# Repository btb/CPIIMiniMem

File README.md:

# Compaq Portable II Mini Memory Expansion

## TODO

More investigation of the possibility of using higher-density SIMMs.

SIMM socket just a smidge too close to the ICs. They'll hit if the ICs use sockets.

Placement of Bank3-4 expanson connector probably renders the nearby mounting hole useless.

Overlap of Bank3-4 expansion connector with SIMM socket not ideal.

SIMM could be turned around and hang over battery.

Can probably make a few mm bigger.

Would be nice if main connector was easier to align.

Find correct size standoffs.

## About

This is a 512K expansion board which connects directly to the motherboard of the Compaq Portable II.

Based on the reverse-engineered [System Memory Board](https://github.com/btb/PortableIIMemBoard).

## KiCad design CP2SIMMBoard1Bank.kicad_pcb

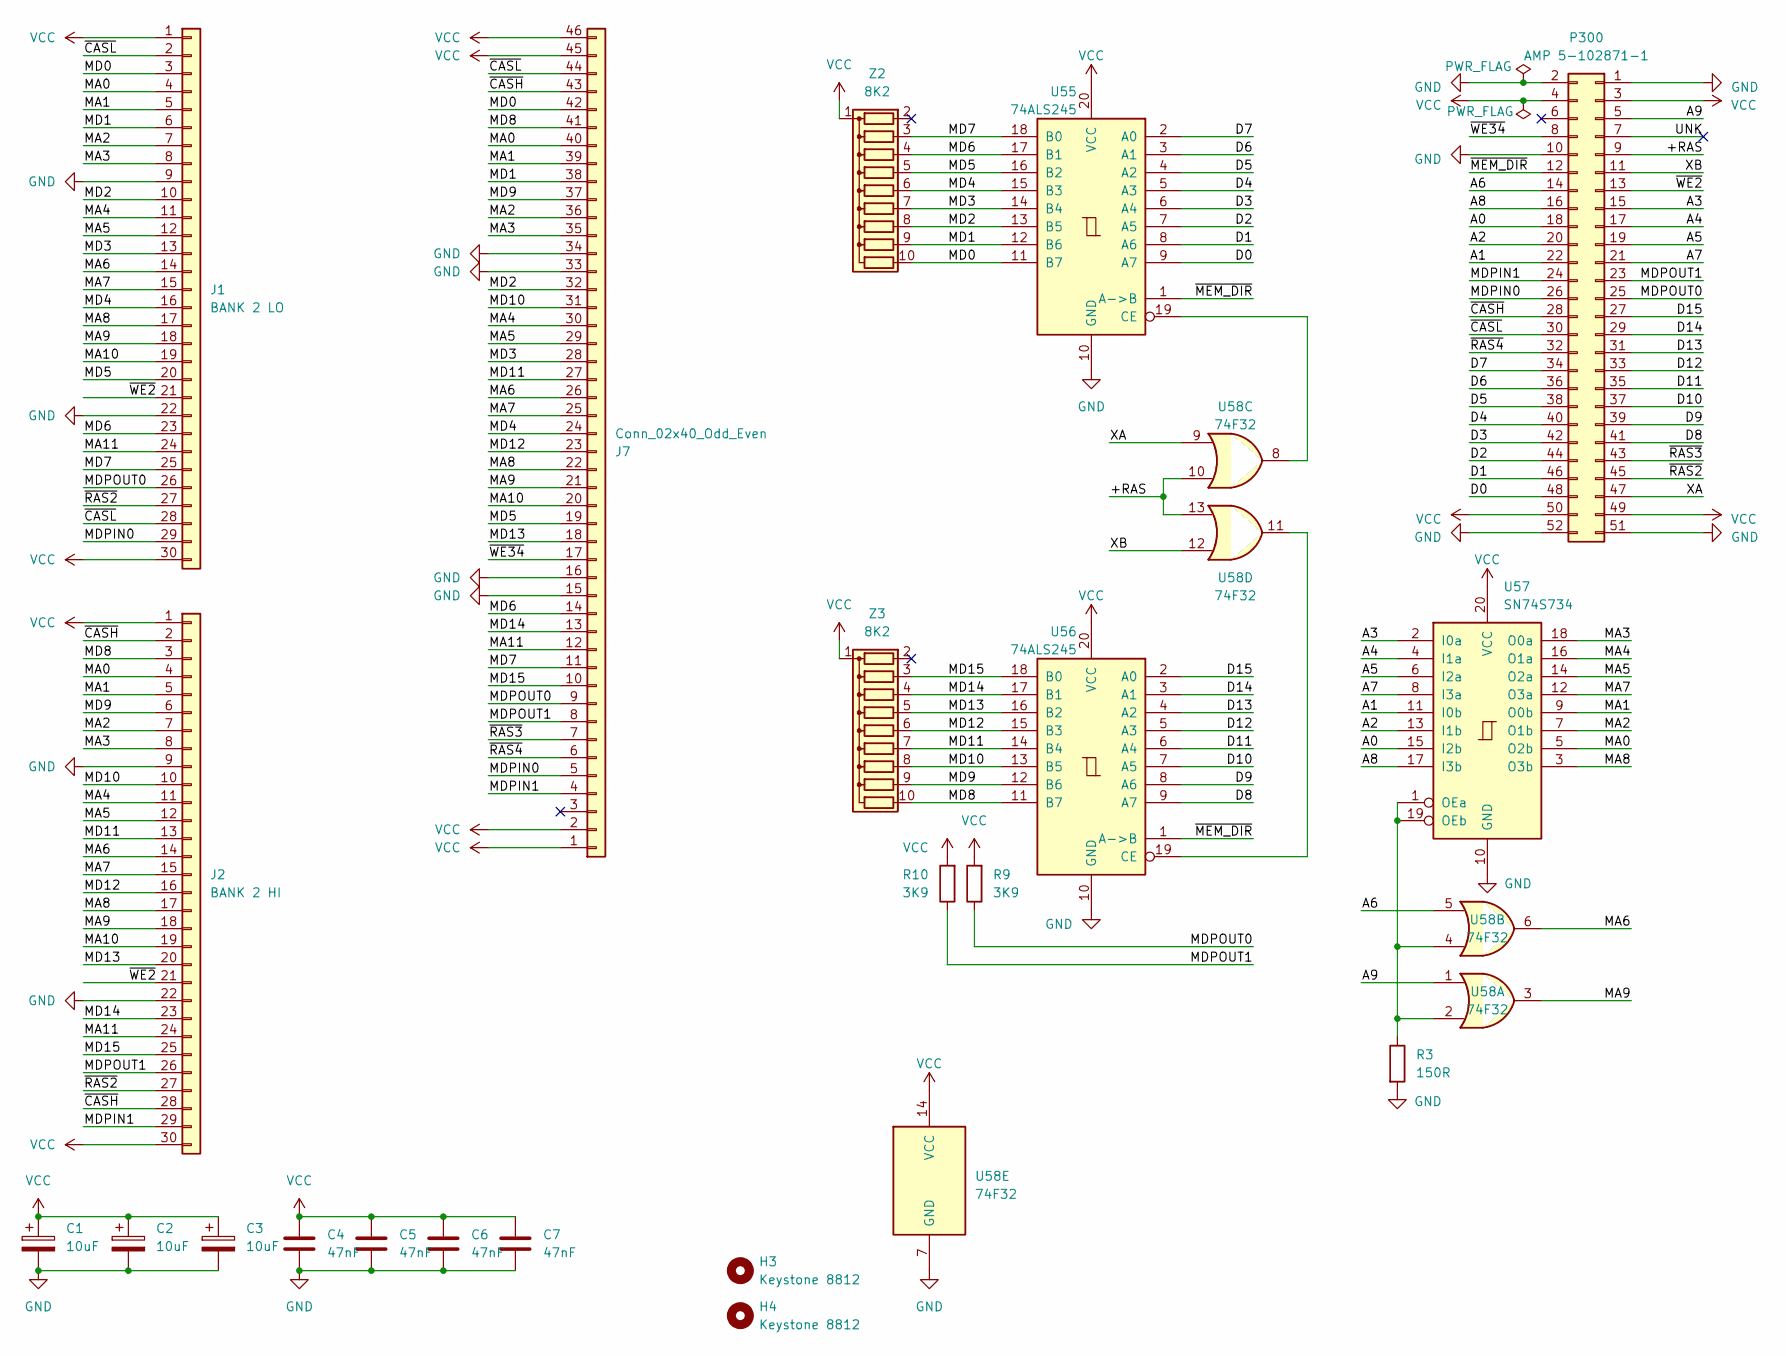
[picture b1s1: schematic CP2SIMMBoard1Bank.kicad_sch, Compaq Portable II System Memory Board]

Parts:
C1, C2, C3: 10uF; CP_Radial_Tantal_D4.5mm_P5.00mm
C4, C5, C6, C7: 47nF; C_Disc_D4.3mm_W1.9mm_P5.00mm
H3, H4: Keystone 8812; MountingHole_4mm
J1: BANK 2 LO; SIMMSocket30Pin
J2: BANK 2 HI; SIMMSocket30Pin
J7: Conn_02x40_Odd_Even; PinSocket_2x23_P2.54mm_Horizontal
P300: AMP 5-102871-1; PinHeader_2x26_P2.54mm_Vertical
R3: 150R; R_Axial_DIN0207_L6.3mm_D2.5mm_P10.16mm_Horizontal
R9, R10: 3K9; R_Axial_DIN0207_L6.3mm_D2.5mm_P10.16mm_Horizontal
U55, U56: 74ALS245; DIP-20_W7.62mm
U57: SN74S734; DIP-20_W7.62mm
U58: 74F32; DIP-14_W7.62mm
Z2, Z3: 8K2; R_Array_SIP10

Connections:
/+RAS: P300.9, U58.10, U58.13
/A0: P300.18, U57.15 (I2b)
/A1: P300.22, U57.11 (I0b)
/A2: P300.20, U57.13 (I1b)
/A3: P300.15, U57.2 (I0a)
/A4: P300.17, U57.4 (I1a)
/A5: P300.19, U57.6 (I2a)
/A6: P300.14, U58.5
/A7: P300.21, U57.8 (I3a)
/A8: P300.16, U57.17 (I3b)
/A9: P300.5, U58.1
/D0: P300.48, U55.9 (A7)
/D1: P300.46, U55.8 (A6)
/D2: P300.44, U55.7 (A5)
/D3: P300.42, U55.6 (A4)
/D4: P300.40, U55.5 (A3)
/D5: P300.38, U55.4 (A2)
/D6: P300.36, U55.3 (A1)
/D7: P300.34, U55.2 (A0)
/D8: P300.41, U56.9 (A7)
/D9: P300.39, U56.8 (A6)
/D10: P300.37, U56.7 (A5)
/D11: P300.35, U56.6 (A4)
/D12: P300.33, U56.5 (A3)
/D13: P300.31, U56.4 (A2)
/D14: P300.29, U56.3 (A1)
/D15: P300.27, U56.2 (A0)
/MA0: J1.4, J2.4, J7.40, U57.5 (O2b)
/MA1: J1.5, J2.5, J7.39, U57.9 (O0b)
/MA2: J1.7, J2.7, J7.36, U57.7 (O1b)
/MA3: J1.8, J2.8, J7.35, U57.18 (O0a)
/MA4: J1.11, J2.11, J7.30, U57.16 (O1a)
/MA5: J1.12, J2.12, J7.29, U57.14 (O2a)
/MA6: J1.14, J2.14, J7.26, U58.6
/MA7: J1.15, J2.15, J7.25, U57.12 (O3a)
/MA8: J1.17, J2.17, J7.22, U57.3 (O3b)
/MA9: J1.18, J2.18, J7.21, U58.3
/MA10: J1.19, J2.19, J7.20
/MA11: J1.24, J2.24, J7.12
/MD0: J1.3, J7.42, U55.11 (B7), Z2.10 (R9)
/MD1: J1.6, J7.38, U55.12 (B6), Z2.9 (R8)
/MD2: J1.10, J7.32, U55.13 (B5), Z2.8 (R7)
/MD3: J1.13, J7.28, U55.14 (B4), Z2.7 (R6)
/MD4: J1.16, J7.24, U55.15 (B3), Z2.6 (R5)
/MD5: J1.20, J7.19, U55.16 (B2), Z2.5 (R4)
/MD6: J1.23, J7.14, U55.17 (B1), Z2.4 (R3)
/MD7: J1.25, J7.11, U55.18 (B0), Z2.3 (R2)
/MD8: J2.3, J7.41, U56.11 (B7), Z3.10 (R9)
/MD9: J2.6, J7.37, U56.12 (B6), Z3.9 (R8)
/MD10: J2.10, J7.31, U56.13 (B5), Z3.8 (R7)
/MD11: J2.13, J7.27, U56.14 (B4), Z3.7 (R6)
/MD12: J2.16, J7.23, U56.15 (B3), Z3.6 (R5)
/MD13: J2.20, J7.18, U56.16 (B2), Z3.5 (R4)
/MD14: J2.23, J7.13, U56.17 (B1), Z3.4 (R3)
/MD15: J2.25, J7.10, U56.18 (B0), Z3.3 (R2)
/MDPIN0: J1.29, J7.5, P300.26
/MDPIN1: J2.29, J7.4, P300.24
/MDPOUT0: J1.26, J7.9, P300.25, R9.1
/MDPOUT1: J2.26, J7.8, P300.23, R10.1
/UNK: P300.7
/XA: P300.47, U58.9
/XB: P300.11, U58.12
/~CASH: J2.2, J2.28, J7.43, P300.28
/~CASL: J1.2, J1.28, J7.44, P300.30
/~MEM_DIR: P300.12, U55.1 (A->B), U56.1 (A->B)
/~RAS2: J1.27, J2.27, P300.45
/~RAS3: J7.7, P300.43
/~RAS4: J7.6, P300.32
/~WE2: J1.21, J2.21, P300.13
/~WE34: J7.17, P300.8
GND: C1.2, C2.2, C3.2, C4.2, C5.2, C6.2, C7.2, J1.9, J1.22, J2.9, J2.22, J7.15, J7.16, J7.33, J7.34, P300.1, P300.2, P300.10, P300.51, P300.52, R3.2, U55.10 (GND), U56.10 (GND), U57.10 (GND), U58.7 (GND)
unnamed: U55.19 (CE), U58.8
unnamed: U56.19 (CE), U58.11
unnamed: R3.1, U57.1 (OEa), U57.19 (OEb), U58.2, U58.4
VCC: C1.1, C2.1, C3.1, C4.1, C5.1, C6.1, C7.1, J1.1, J1.30, J2.1, J2.30, J7.1, J7.2, J7.45, J7.46, P300.3, P300.4, P300.49, P300.50, R9.2, R10.2, U55.20 (VCC), U56.20 (VCC), U57.20 (VCC), U58.14 (VCC), Z2.1 (common), Z3.1 (common)

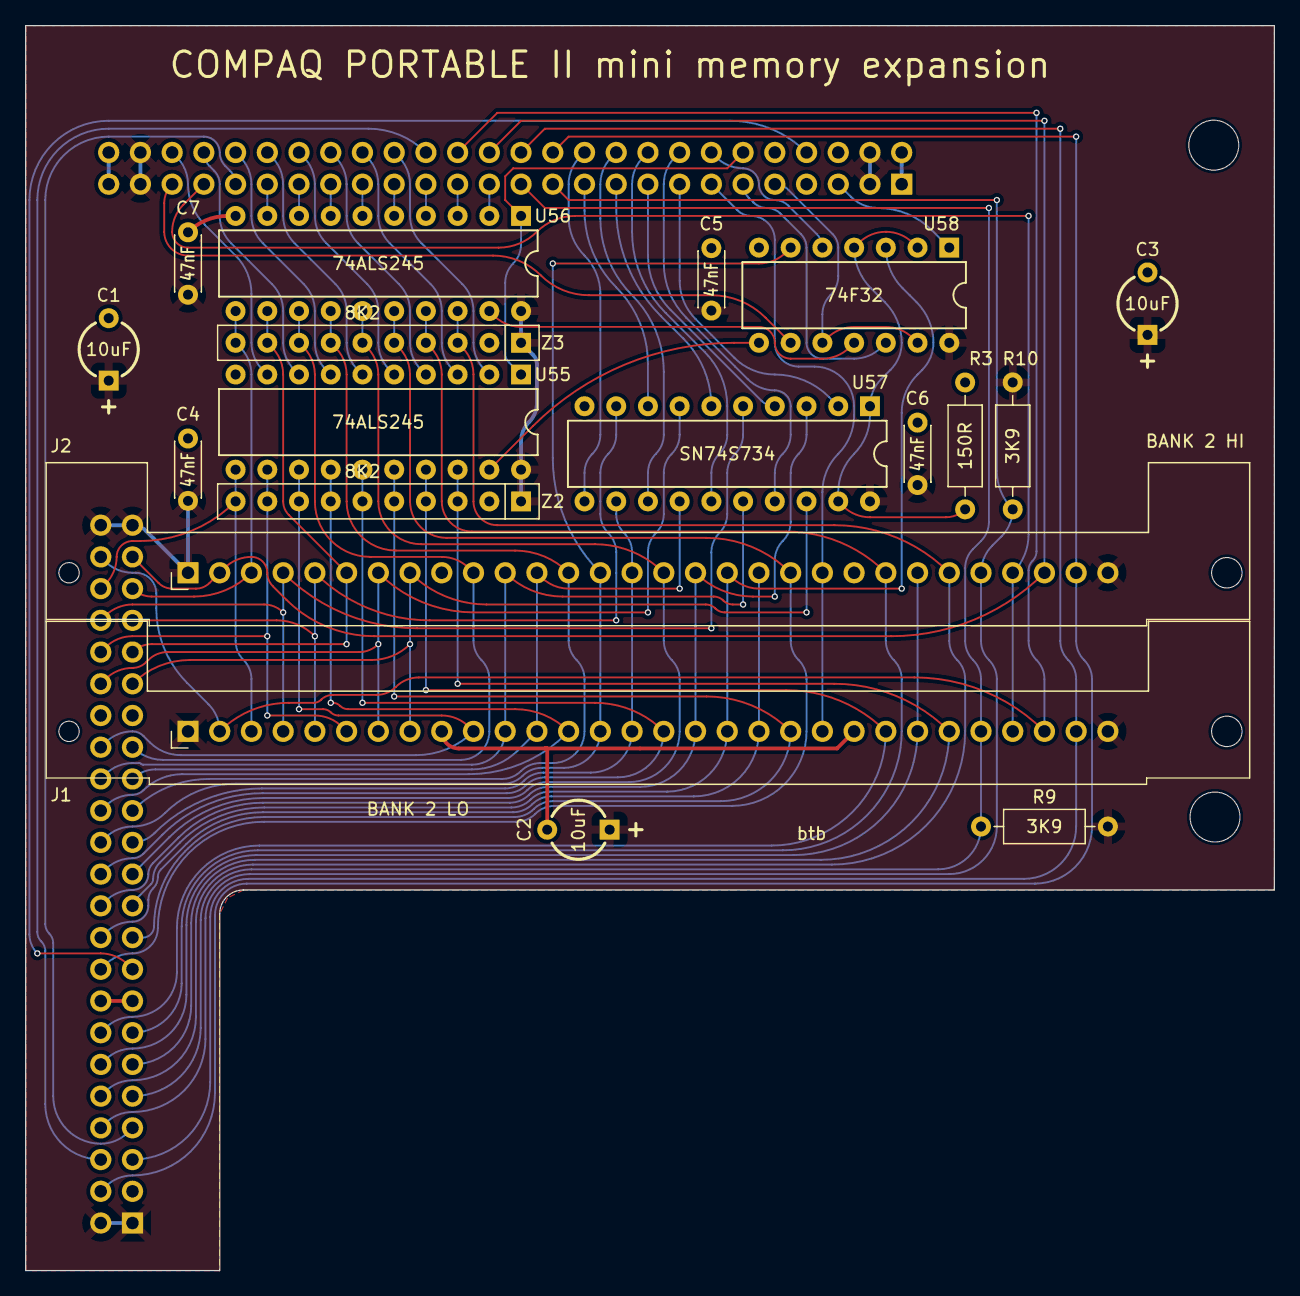
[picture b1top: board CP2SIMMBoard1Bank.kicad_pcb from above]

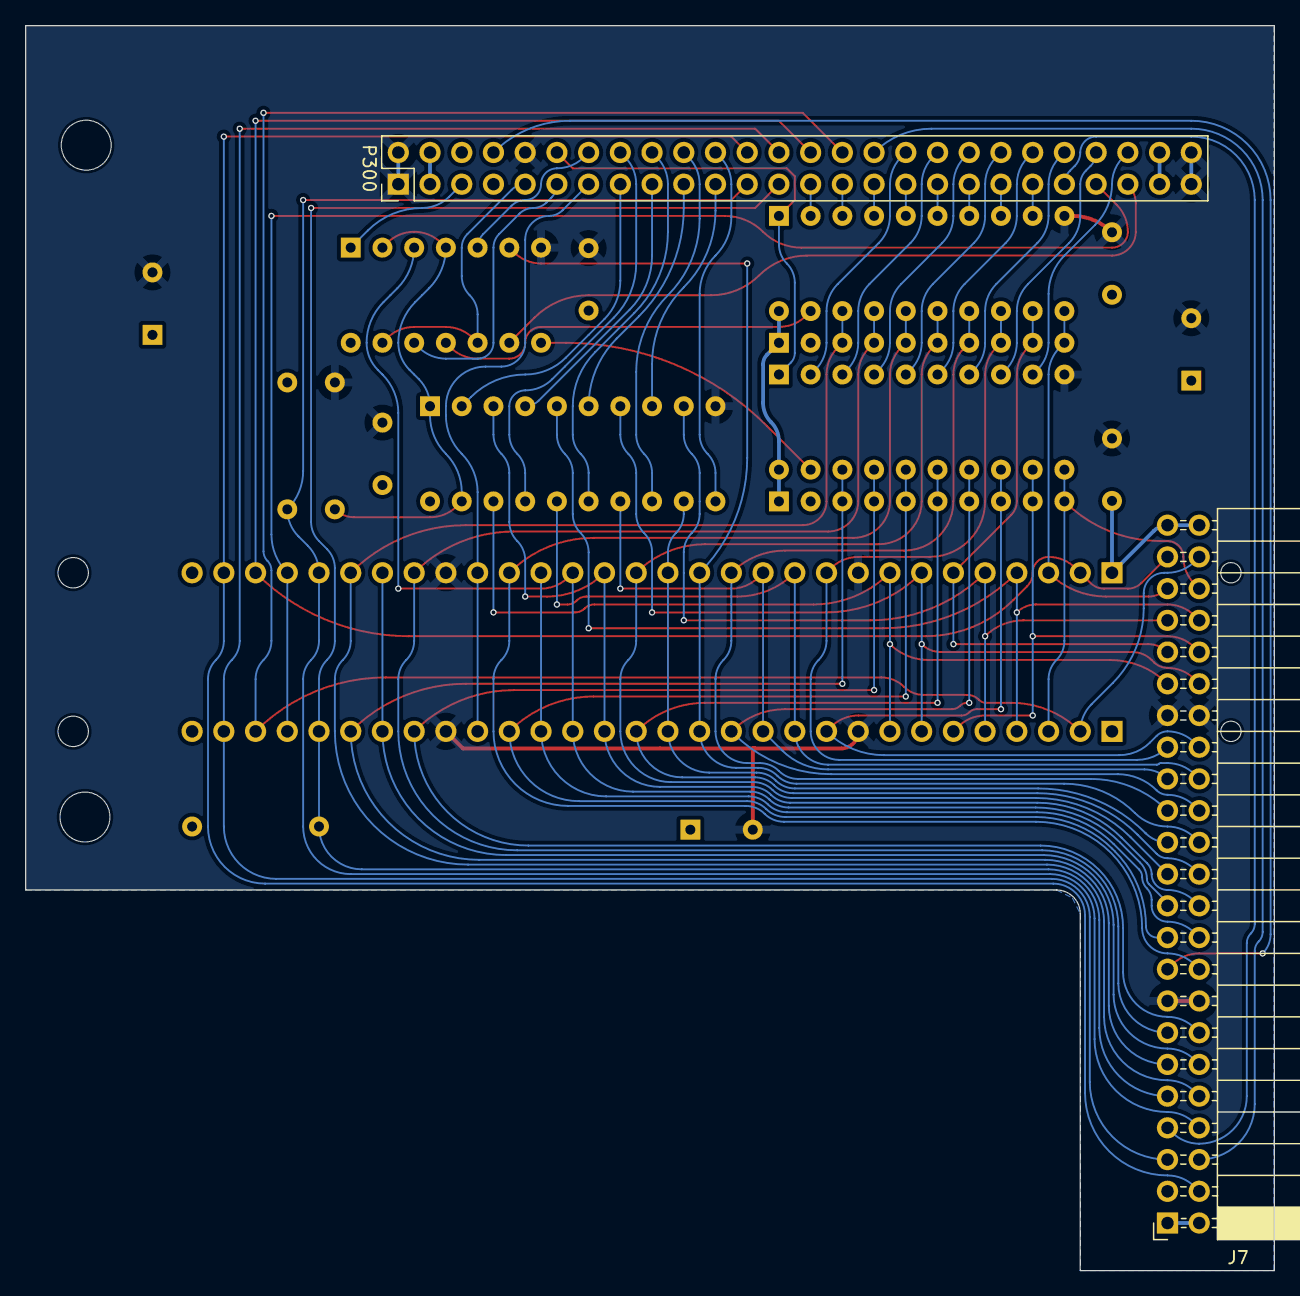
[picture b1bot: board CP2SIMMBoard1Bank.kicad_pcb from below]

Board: 2 copper layers, 100.0 x 99.7 mm, 22 parts (2 on the bottom side), 74 nets.

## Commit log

2024-04-16 Initial 2-simm prototype
